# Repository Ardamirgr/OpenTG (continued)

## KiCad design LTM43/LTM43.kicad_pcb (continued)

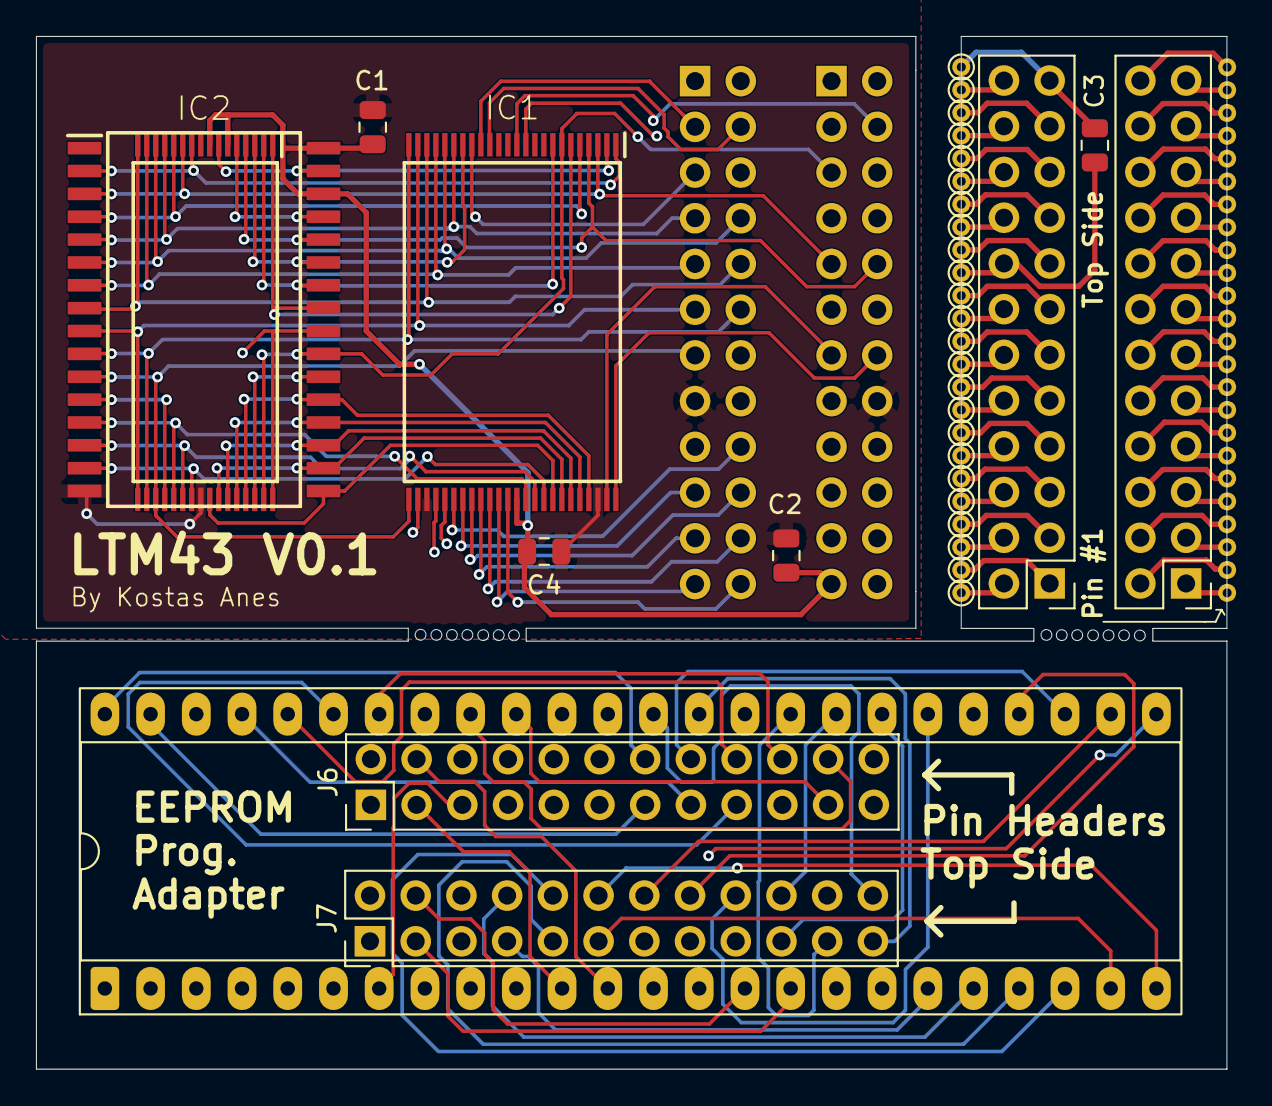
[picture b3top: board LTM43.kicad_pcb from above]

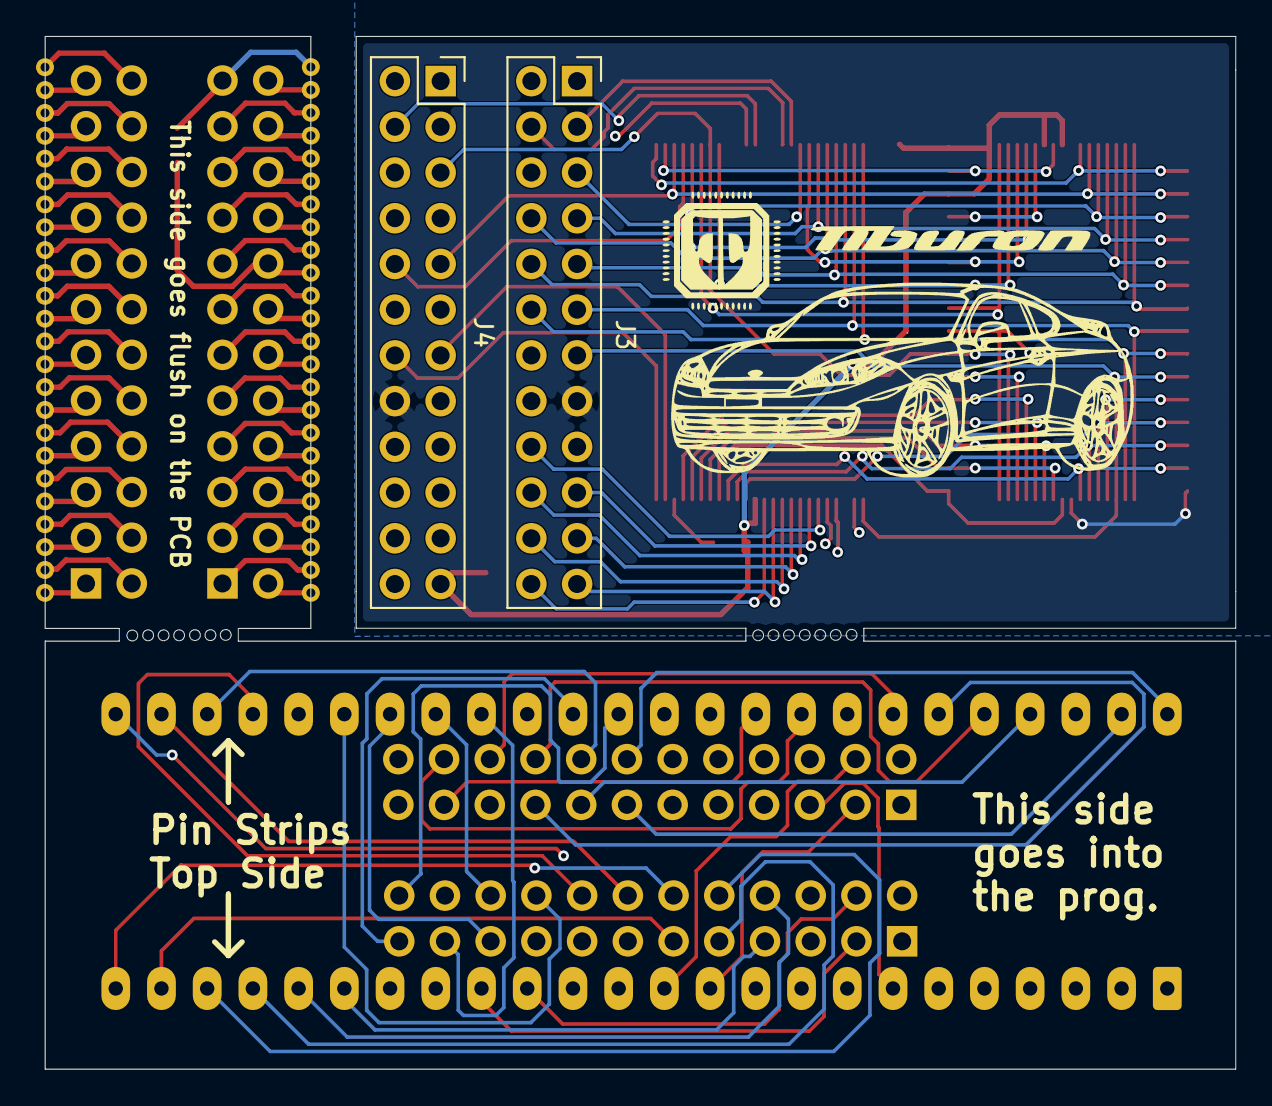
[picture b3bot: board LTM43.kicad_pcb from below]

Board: 4 copper layers, 66.1 x 57.4 mm, 62 parts (2 on the bottom side), 47 nets.

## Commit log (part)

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2026-01-24 Create Firmware
2026-01-24 Upload v1.0 and v1.1 (not yet finished) versions of firmware
2026-01-24 Add XBM icons used in the project
2026-01-24 Added PCB and schematic files
2026-01-24 Create foo
2026-02-03 Update PCBs to latest version
    Gauge:
    -- Changed FTDI 232RNL to FTDI 231XS (60% cheaper, smaller size, no need of extra features of the 232).
    -- Introduced gound plane to help with EMI immunity (noticed on buttons on very rare cases).
    -- Optimized capacitor placement and some trace routing.
    Mainboard:
    -- Introduced a proper DIP connector for programming.
2026-02-04 v0.1 PCB
2026-02-09 Fix upside down connector
2026-03-11 QoL changes for optimizing production
2026-03-11 Changed layout to include ground plane and some capacitors moved
2026-03-11 v0.2 PCB
2026-04-16 v0.1 firmware for Controller board
    Gauge is pre-alpha and an abandoned design choice. Will get to developing it after the controller board is confirmed working.
2026-04-19 v0.2 of the firmware, added gauge firmware
2026-04-19 Datasheets for sensors
2026-04-19 Python software for uploading profiles.
    No such function yet, will be added after the current controller has been tested and is working ok.
2026-04-19 V1.0 of the mainboard files
2026-05-02 Uploaded the files for the MAF adapter board
2026-06-03 48mm Gauge and Mainboard updates
2026-06-03 Mainboard power supply and QoL updates.
2026-06-03 Shrinked to 48.6mm for more space for the casing
2026-06-03 Small fixes v0.2
2026-06-05 Major updates for safe handling of boost control, sensors etc
2026-06-05 Name change
